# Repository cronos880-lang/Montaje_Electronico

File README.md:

# Montaje Electrónico

Repositorio del Controlador de Acuario. Los diseños se preparan en ramas de trabajo para su revisión.

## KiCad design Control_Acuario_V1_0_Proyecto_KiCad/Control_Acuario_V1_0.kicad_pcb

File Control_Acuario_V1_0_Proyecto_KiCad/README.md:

# Controlador de Acuario V1.0

**Revisión B: esquema y PCB trazada, pendientes de aprobación y ensayos.** Abrir `Control_Acuario_V1_0.kicad_pro` con KiCad 9. El PDF permite revisar el circuito sin instalar KiCad. La revisión A está en el ZIP `Control_Acuario_V1_0_Revision_A.zip` y en el commit `4b8fed1`.

## Para revisar
- [Esquema en PDF (rev. B)](Control_Acuario_V1_0_Esquema.pdf)
- [PCB y guía de fabricación (coste, cómo pedir)](Control_Acuario_V1_0_PCB_y_Fabricacion.md)
- [Revisión final antes del pedido](Control_Acuario_V1_0_Revision_Final_Prepedido.md)
- [Vista 3D cara superior](Control_Acuario_V1_0_PCB_3D_superior.png) · [PDF cara superior](Control_Acuario_V1_0_PCB_cara_superior.pdf) · [PDF cara inferior](Control_Acuario_V1_0_PCB_cara_inferior.pdf)
- [Informe DRC (KiCad 9.0.9)](Control_Acuario_V1_0_DRC.rpt)
- [Archivos de fabricación](fabricacion/)
- [Revisión B: correcciones, cálculos y pendientes](Control_Acuario_V1_0_Revision_B.md)
- [Lista de componentes con referencias LCSC (rev. B)](Control_Acuario_V1_0_BOM.csv)
- [Informe ERC (KiCad 9.0.9)](Control_Acuario_V1_0_ERC.rpt)
- [Revisión A: informe original](Control_Acuario_V1_0_Revision_ERC_DRC.md)
- [Plan de pruebas](Control_Acuario_V1_0_Plan_Pruebas.md)

## Alcance
Una salida de dos polos para luz monocolor, con consigna de tensión (≈5–24 V) y PWM independientes. Dos mandos DC para SSR externos, ESP32-DevKitC-32E con Wi-Fi y Bluetooth, reloj DS3231 extraíble y sonda DS18B20. La PCB solo lleva baja tensión: bomba y calentador de 230 V van en SSR externos, y su integración la valida un profesional cualificado.

PCB trazada con DRC limpio (solo avisos de serigrafía) y archivos de fabricación generados. Pendientes: tu revisión, las pruebas de banco y el firmware. No se ha hecho ningún pedido.

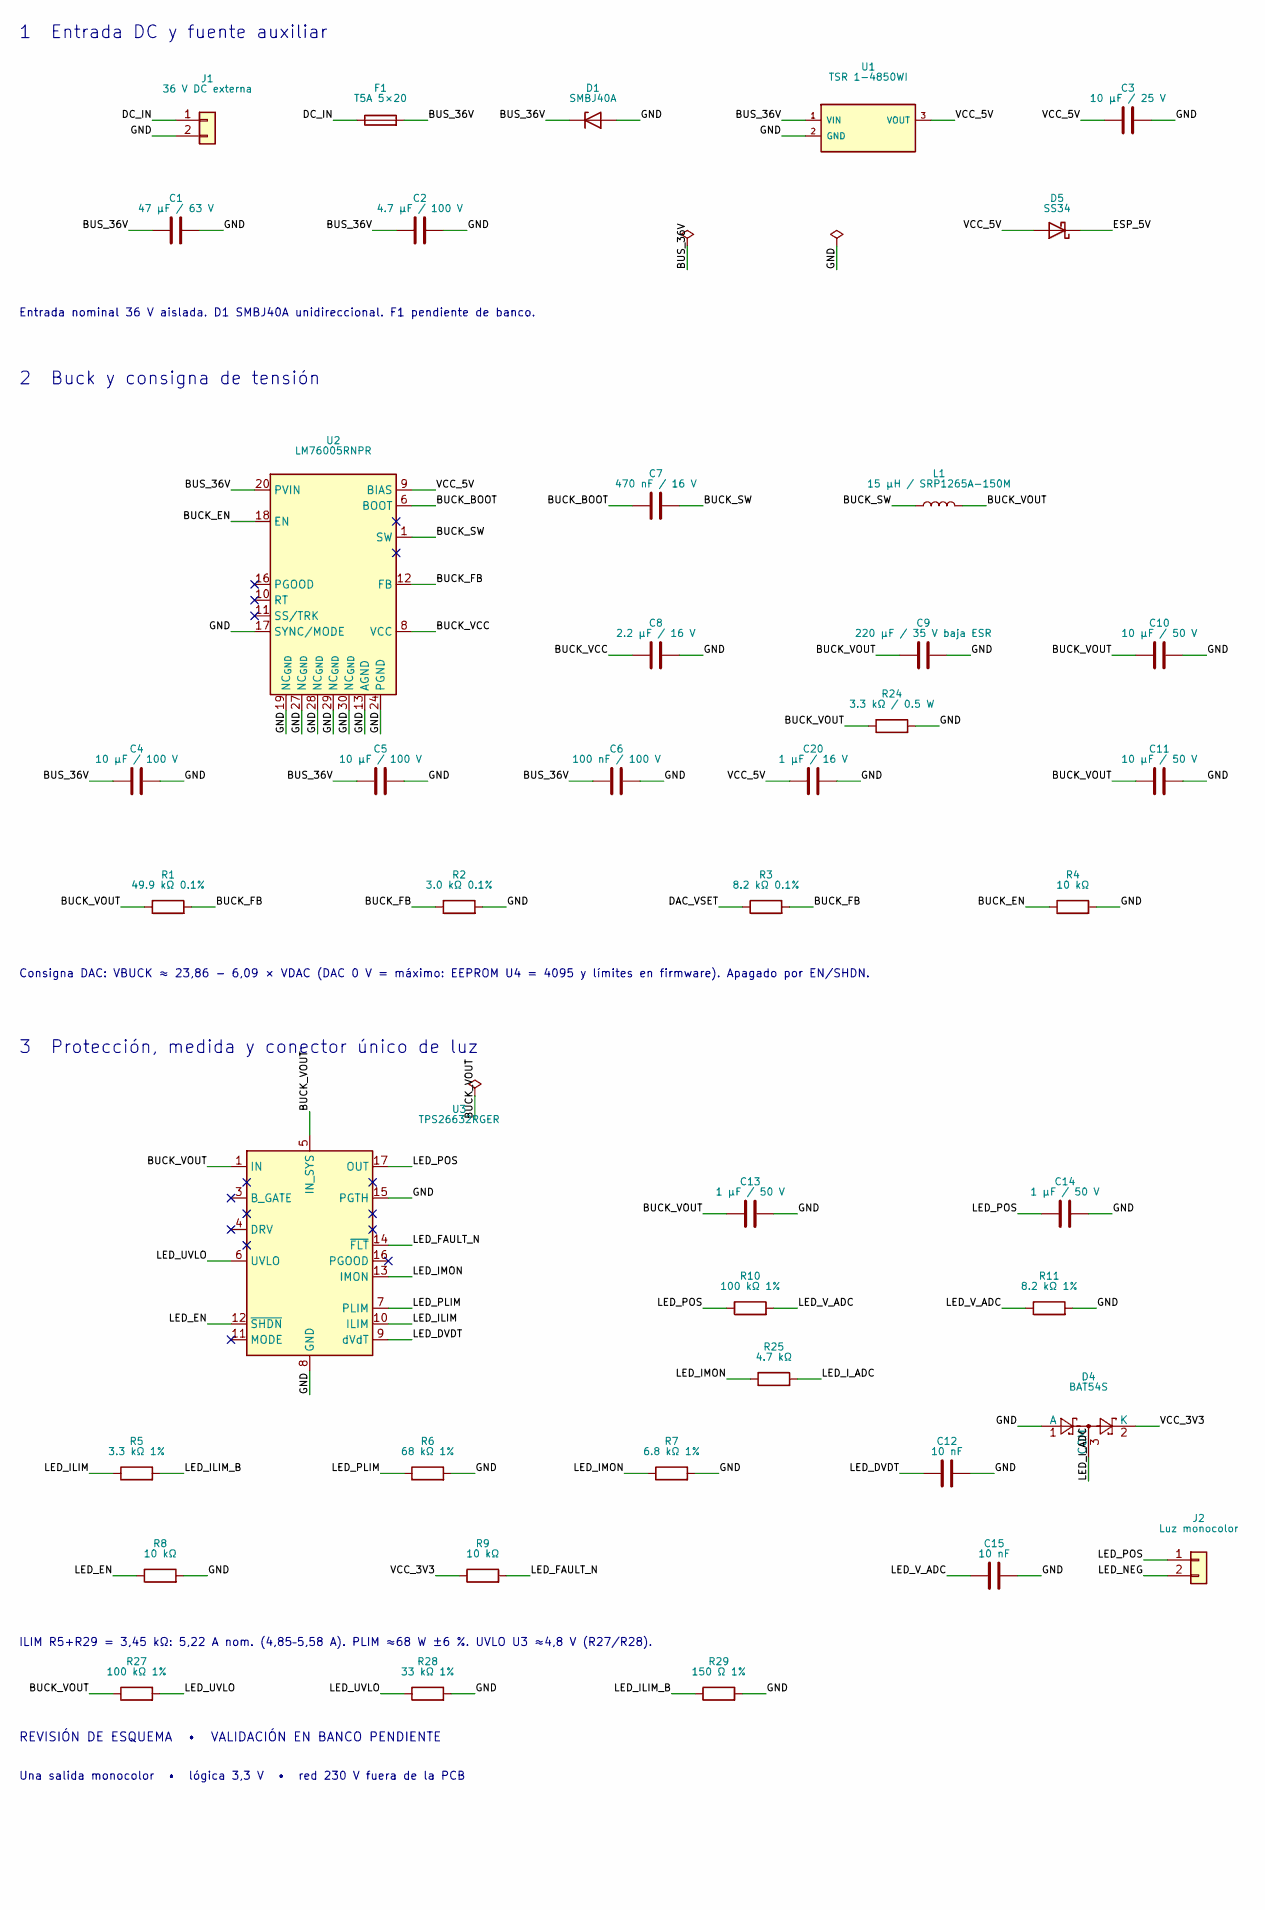
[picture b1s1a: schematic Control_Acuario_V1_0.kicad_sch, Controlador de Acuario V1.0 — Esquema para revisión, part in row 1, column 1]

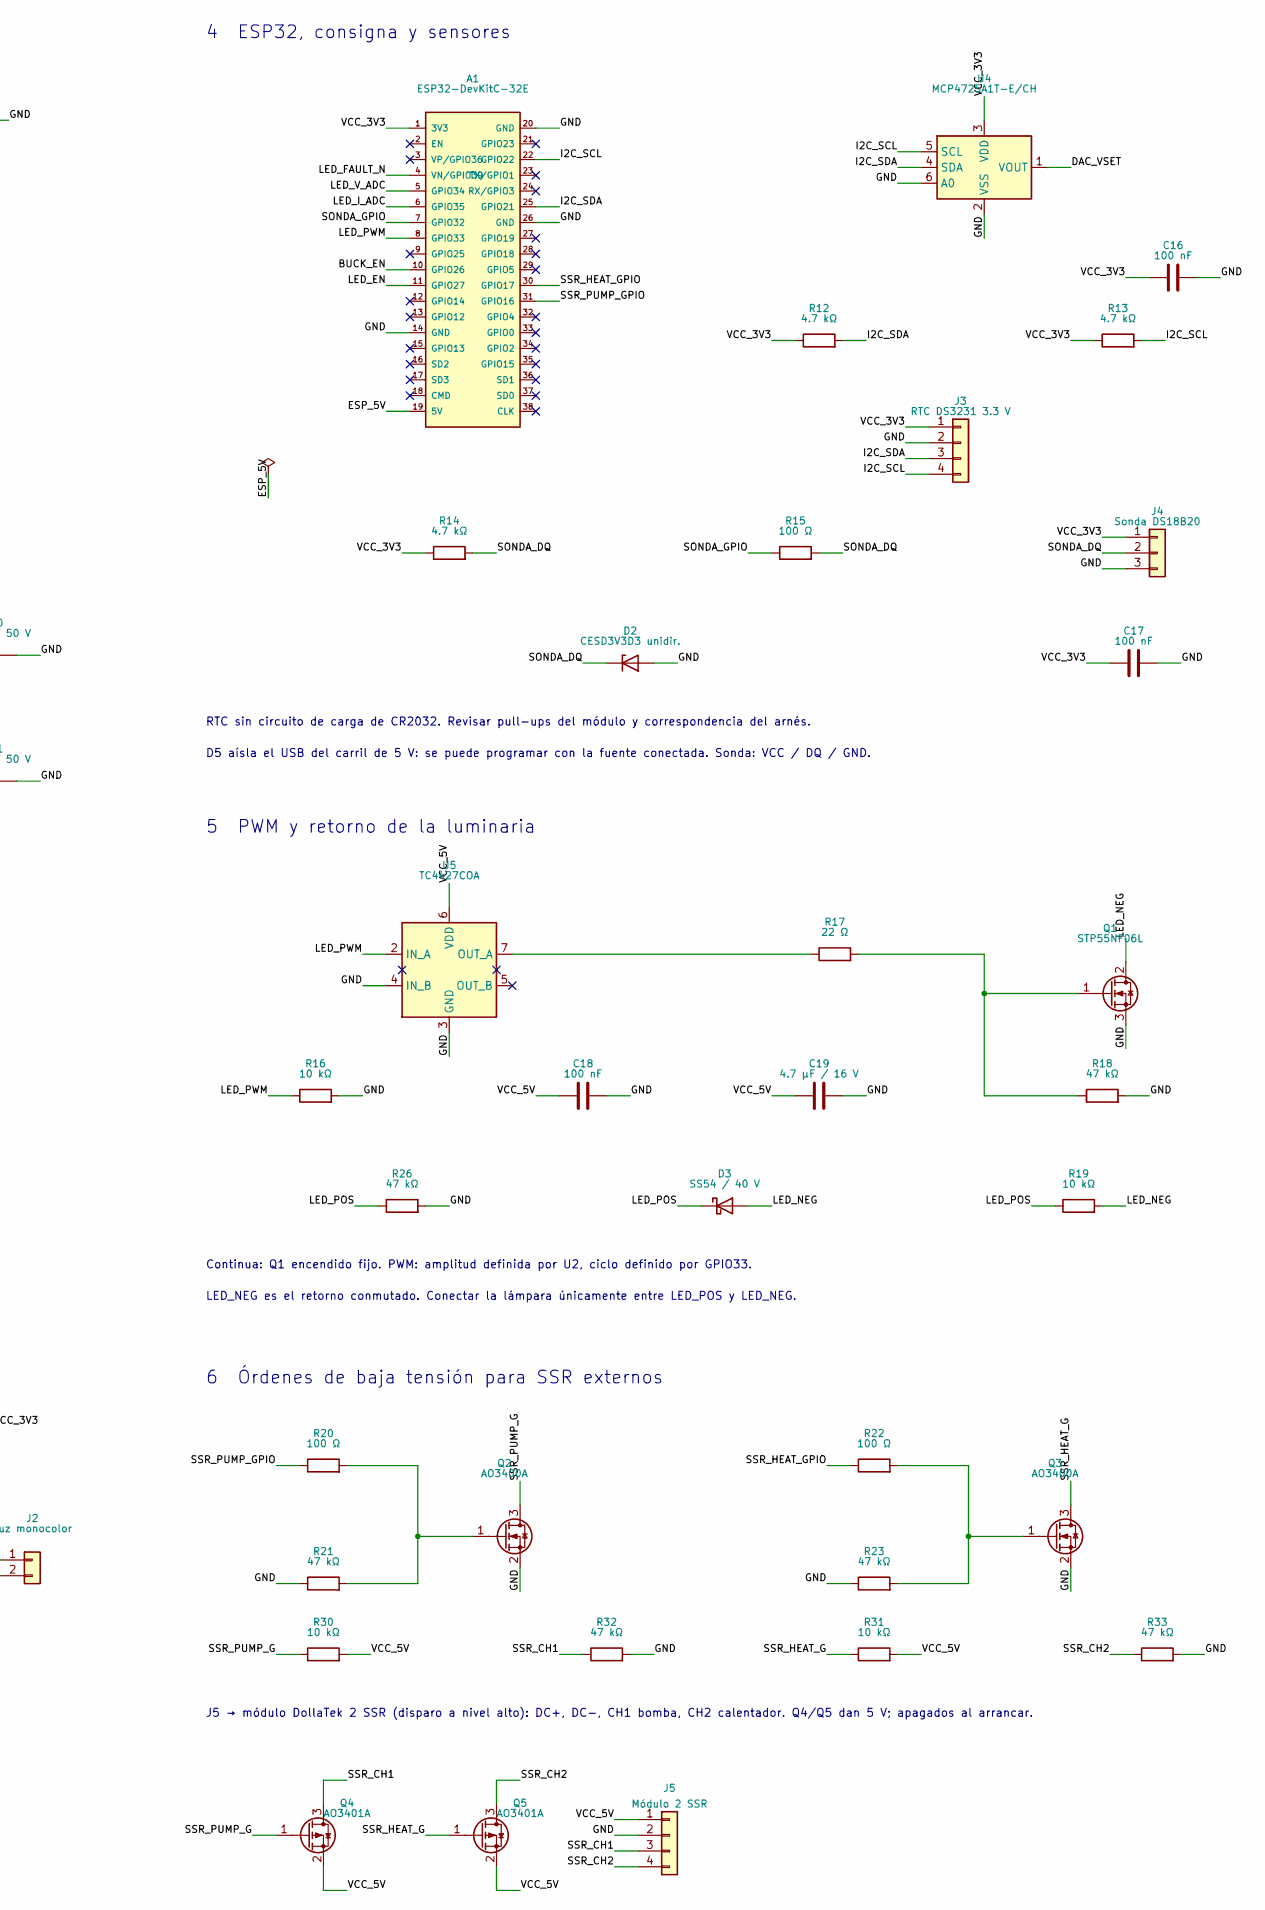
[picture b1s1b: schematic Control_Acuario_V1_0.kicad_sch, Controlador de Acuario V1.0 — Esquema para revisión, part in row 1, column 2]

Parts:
A1: ESP32-DevKitC-32E; ESP32_DevKitC_V4_Zocalo
C1: 47 µF / 63 V; CP_Radial_D8.0mm_P3.50mm
C2: 4.7 µF / 100 V; C_1210_3225Metric
C3: 10 µF / 25 V; C_0805_2012Metric
C4, C5: 10 µF / 100 V; C_1210_3225Metric
C6: 100 nF / 100 V; C_0805_2012Metric
C7: 470 nF / 16 V; C_0805_2012Metric
C8: 2.2 µF / 16 V; C_0805_2012Metric
C9: 220 µF / 35 V baja ESR; CP_Radial_D8.0mm_P3.50mm
C10, C11: 10 µF / 50 V; C_1210_3225Metric
C12, C15: 10 nF; C_0805_2012Metric
C13, C14: 1 µF / 50 V; C_0805_2012Metric
C16, C17, C18: 100 nF; C_0805_2012Metric
C19: 4.7 µF / 16 V; C_0805_2012Metric
C20: 1 µF / 16 V; C_0805_2012Metric
D1: SMBJ40A; D_SMB
D2: CESD3V3D3 unidir.; D_SOD-323
D3: SS54 / 40 V; D_SMA
D4: BAT54S; SOT-23
D5: SS34; D_SMA
F1: T5A 5×20; Fuseholder_Clip-5x20mm_Littelfuse_111_Inline_P20.00x5.00mm_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
J1: 36 V DC externa; TerminalBlock_Phoenix_MKDS-1,5-2-5.08_1x02_P5.08mm_Horizont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
J2: Luz monocolor; TerminalBlock_Phoenix_MKDS-1,5-2-5.08_1x02_P5.08mm_Horizont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
J3: RTC DS3231 3.3 V; PinHeader_1x04_P2.54mm_Vertical
J4: Sonda DS18B20; PinHeader_1x03_P2.54mm_Vertical
J5: Módulo 2 SSR; PinHeader_1x04_P2.54mm_Vertical
L1: 15 µH / SRP1265A-150M; L_Bourns_SRP1245A
Q1: STP55NF06L; TO-220-3_Vertical
Q2, Q3: AO3400A; SOT-23
Q4, Q5: AO3401A; SOT-23
R1: 49.9 kΩ 0.1%; R_0805_2012Metric
R2: 3.0 kΩ 0.1%; R_0805_2012Metric
R3: 8.2 kΩ 0.1%; R_0805_2012Metric
R4, R8, R9, R16, R30, R31: 10 kΩ; R_0805_2012Metric
R5: 3.3 kΩ 1%; R_0805_2012Metric
R6: 68 kΩ 1%; R_0805_2012Metric
R7: 6.8 kΩ 1%; R_0805_2012Metric
R10, R27: 100 kΩ 1%; R_0805_2012Metric
R11: 8.2 kΩ 1%; R_0805_2012Metric
R12, R13, R14, R25: 4.7 kΩ; R_0805_2012Metric
R15, R20, R22: 100 Ω; R_0805_2012Metric
R17: 22 Ω; R_0805_2012Metric
R18, R21, R23, R26, R32, R33: 47 kΩ; R_0805_2012Metric
R19: 10 kΩ; R_1206_3216Metric
R24: 3.3 kΩ / 0.5 W; R_2010_5025Metric
R28: 33 kΩ 1%; R_0805_2012Metric
R29: 150 Ω 1%; R_0805_2012Metric
U1: TSR 1-4850WI; Converter_DCDC_TRACO_TSR-1_THT
U2: LM76005RNPR; Texas_RNP0030B_WQFN-30-1EP_4x6mm_P0.5mm_EP1.8x4.5mm
U3: TPS26632RGER; Texas_RGE0024H_VQFN-24-1EP_4x4mm_P0.5mm_EP2.7x2.7mm
U4: MCP4725A1T-E/CH; SOT-23-6
U5: TC4427COA; SOIC-8_3.9x4.9mm_P1.27mm

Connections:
/BUCK_BOOT: C7.1, U2.6 (BOOT)
/BUCK_EN: A1.10 (GPIO26), R4.1, U2.18 (EN)
/BUCK_FB: R1.2, R2.1, R3.2, U2.12 (FB)
/BUCK_SW: C7.2, L1.1, U2.1 (SW), U2.2 (SW), U2.3 (SW), U2.4 (SW), U2.5 (SW)
/BUCK_VCC: C8.1, U2.8 (VCC)
/BUCK_VOUT: C9.1, C10.1, C11.1, C13.1, L1.2, R1.1, R24.1, R27.1, U3.1 (IN), U3.2 (IN), U3.5 (IN_SYS)
/BUS_36V: C1.1, C2.1, C4.1, C5.1, C6.1, D1.1 (K), F1.2, U1.1 (VIN), U2.20 (PVIN), U2.21 (PVIN), U2.22 (PVIN)
/DAC_VSET: R3.1, U4.1 (VOUT)
/DC_IN: F1.1, J1.1
/ESP_5V: A1.19 (5V), D5.1 (K)
/GND: A1.14 (GND), A1.20 (GND), A1.26 (GND), C1.2, C2.2, C3.2, C4.2, C5.2, C6.2, C8.2, C9.2, C10.2, C11.2, C12.2, C13.2, C14.2, C15.2, C16.2, C17.2, C18.2, C19.2, C20.2, D1.2 (A), D2.2 (A), D4.1 (A), J1.2, J3.2, J4.3, J5.2, Q1.3 (S), Q2.2 (S), Q3.2 (S), R2.2, R4.2, R6.2, R7.2, R8.2, R11.2, R16.2, R18.2, R21.1, R23.1, R24.2, R26.2, R28.2, R29.2, R32.2, R33.2, U1.2 (GND), U2.13 (AGND), U2.14 (AGND), U2.15 (AGND), U2.17 (SYNC/MODE), U2.19 (NC_{GND}), U2.24 (PGND), U2.25 (PGND), U2.26 (PGND), U2.27 (NC_{GND}), U2.28 (NC_{GND}), U2.29 (NC_{GND}), U2.30 (NC_{GND}), U2.31 (AGND), U3.8 (GND), U3.15 (PGTH), U3.25 (GND), U4.2 (VSS), U4.6 (A0), U5.3 (GND), U5.4 (IN_B)
/I2C_SCL: A1.22 (GPIO22), J3.4, R13.2, U4.5 (SCL)
/I2C_SDA: A1.25 (GPIO21), J3.3, R12.2, U4.4 (SDA)
/LED_DVDT: C12.1, U3.9 (dVdT)
/LED_EN: A1.11 (GPIO27), R8.1, U3.12 (~SHDN)
/LED_FAULT_N: A1.4 (VN/GPIO39), R9.2, U3.14 (~FLT)
/LED_ILIM: R5.1, U3.10 (ILIM)
/LED_ILIM_B: R5.2, R29.1
/LED_IMON: R7.1, R25.1, U3.13 (IMON)
/LED_I_ADC: A1.6 (GPIO35), D4.3 (COM), R25.2
/LED_NEG: D3.2 (A), J2.2, Q1.2 (D), R19.2
/LED_PLIM: R6.1, U3.7 (PLIM)
/LED_POS: C14.1, D3.1 (K), J2.1, R10.1, R19.1, R26.1, U3.17 (OUT), U3.18 (OUT)
/LED_PWM: A1.8 (GPIO33), R16.1, U5.2 (IN_A)
/LED_UVLO: R27.2, R28.1, U3.6 (UVLO)
/LED_V_ADC: A1.5 (GPIO34), C15.1, R10.2, R11.1
/SONDA_DQ: D2.1 (K), J4.2, R14.2, R15.2
/SONDA_GPIO: A1.7 (GPIO32), R15.1
/SSR_CH1: J5.3, Q4.3 (D), R32.1
/SSR_CH2: J5.4, Q5.3 (D), R33.1
/SSR_HEAT_G: Q3.3 (D), Q5.1 (G), R31.1
/SSR_HEAT_GPIO: A1.30 (GPIO17), R22.1
/SSR_PUMP_G: Q2.3 (D), Q4.1 (G), R30.1
/SSR_PUMP_GPIO: A1.31 (GPIO16), R20.1
/VCC_3V3: A1.1 (3V3), C16.1, C17.1, D4.2 (K), J3.1, J4.1, R9.1, R12.1, R13.1, R14.1, U4.3 (VDD)
/VCC_5V: C3.1, C18.1, C19.1, C20.1, D5.2 (A), J5.1, Q4.2 (S), Q5.2 (S), R30.2, R31.2, U1.3 (VOUT), U2.9 (BIAS), U5.6 (VDD)
unnamed: Q1.1 (G), R17.2, R18.1
unnamed: Q2.1 (G), R20.2, R21.2
unnamed: Q3.1 (G), R22.2, R23.2
unnamed: R17.1, U5.7 (OUT_A)

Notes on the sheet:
1 Entrada DC y fuente auxiliar
Entrada nominal 36 V aislada. D1 SMBJ40A unidireccional. F1 pendiente de banco.
2 Buck y consigna de tensión
Consigna DAC: VBUCK ≈ 23,86 − 6,09 × VDAC (DAC 0 V = máximo: EEPROM U4 = 4095 y límites en firmware). Apagado por EN/SHDN.
3 Protección, medida y conector único de luz
ILIM R5+R29 = 3,45 kΩ: 5,22 A nom. (4,85–5,58 A). PLIM ≈68 W ±6 %. UVLO U3 ≈4,8 V (R27/R28).
4 ESP32, consigna y sensores
RTC sin circuito de carga de CR2032. Revisar pull-ups del módulo y correspondencia del arnés.
D5 aísla el USB del carril de 5 V: se puede programar con la fuente conectada. Sonda: VCC / DQ / GND.
5 PWM y retorno de la luminaria
Continua: Q1 encendido fijo. PWM: amplitud definida por U2, ciclo definido por GPIO33.
LED_NEG es el retorno conmutado. Conectar la lámpara únicamente entre LED_POS y LED_NEG.
6 Órdenes de baja tensión para SSR externos
J5 → módulo DollaTek 2 SSR (disparo a nivel alto): DC+, DC−, CH1 bomba, CH2 calentador. Q4/Q5 dan 5 V; apagados al arrancar.
REVISIÓN DE ESQUEMA • VALIDACIÓN EN BANCO PENDIENTE
Una salida monocolor • lógica 3,3 V • red 230 V fuera de la PCB

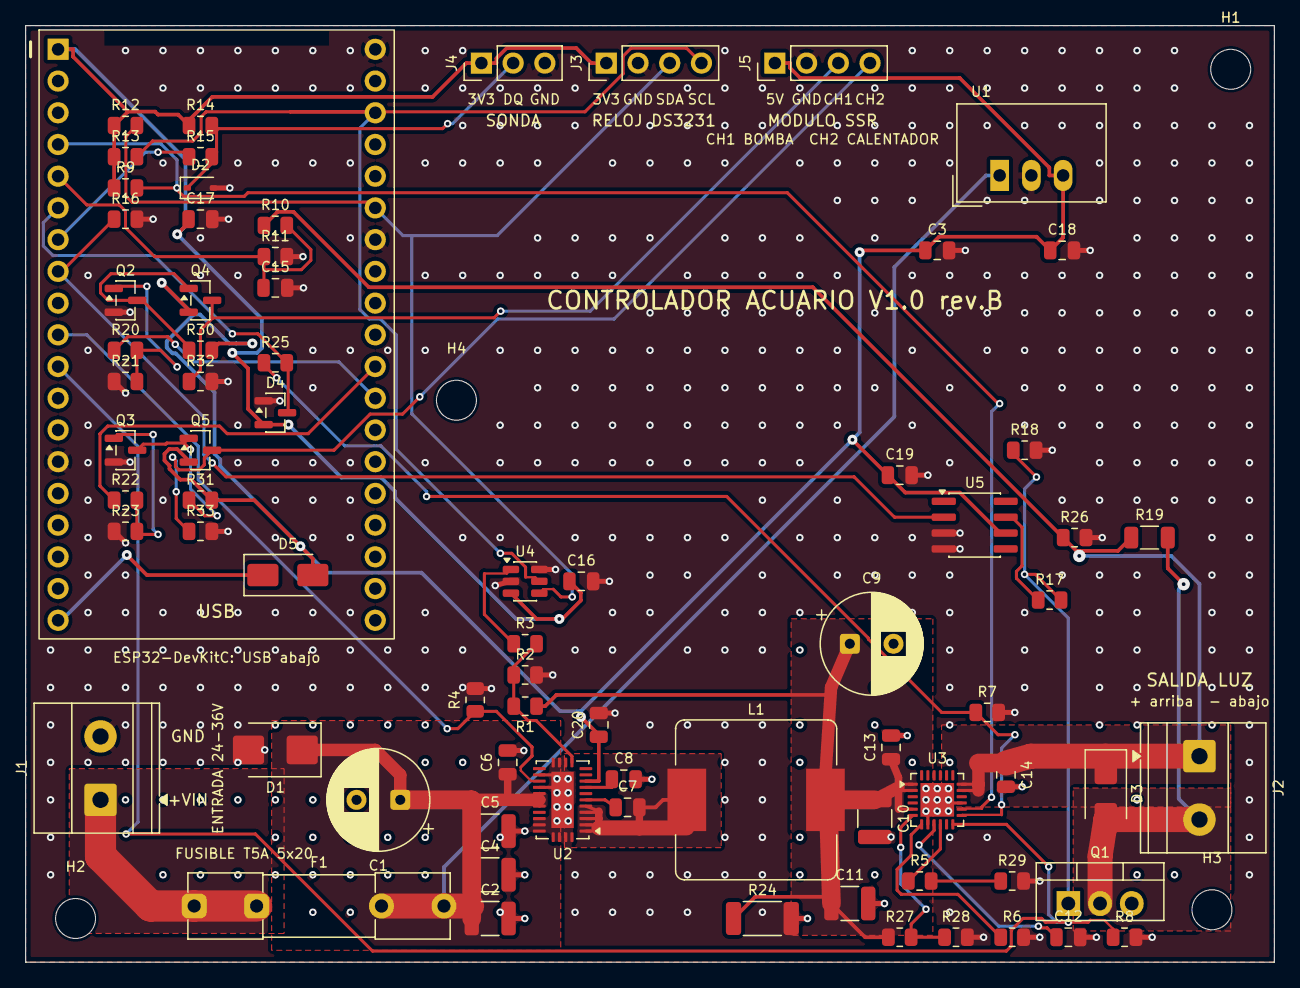
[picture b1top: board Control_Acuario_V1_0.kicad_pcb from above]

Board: 2 copper layers, 100.0 x 75.0 mm, 80 parts (0 on the bottom side), 40 nets.

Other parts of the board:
H1, H2, H3, H4: MountingHole_3.2mm_M3
